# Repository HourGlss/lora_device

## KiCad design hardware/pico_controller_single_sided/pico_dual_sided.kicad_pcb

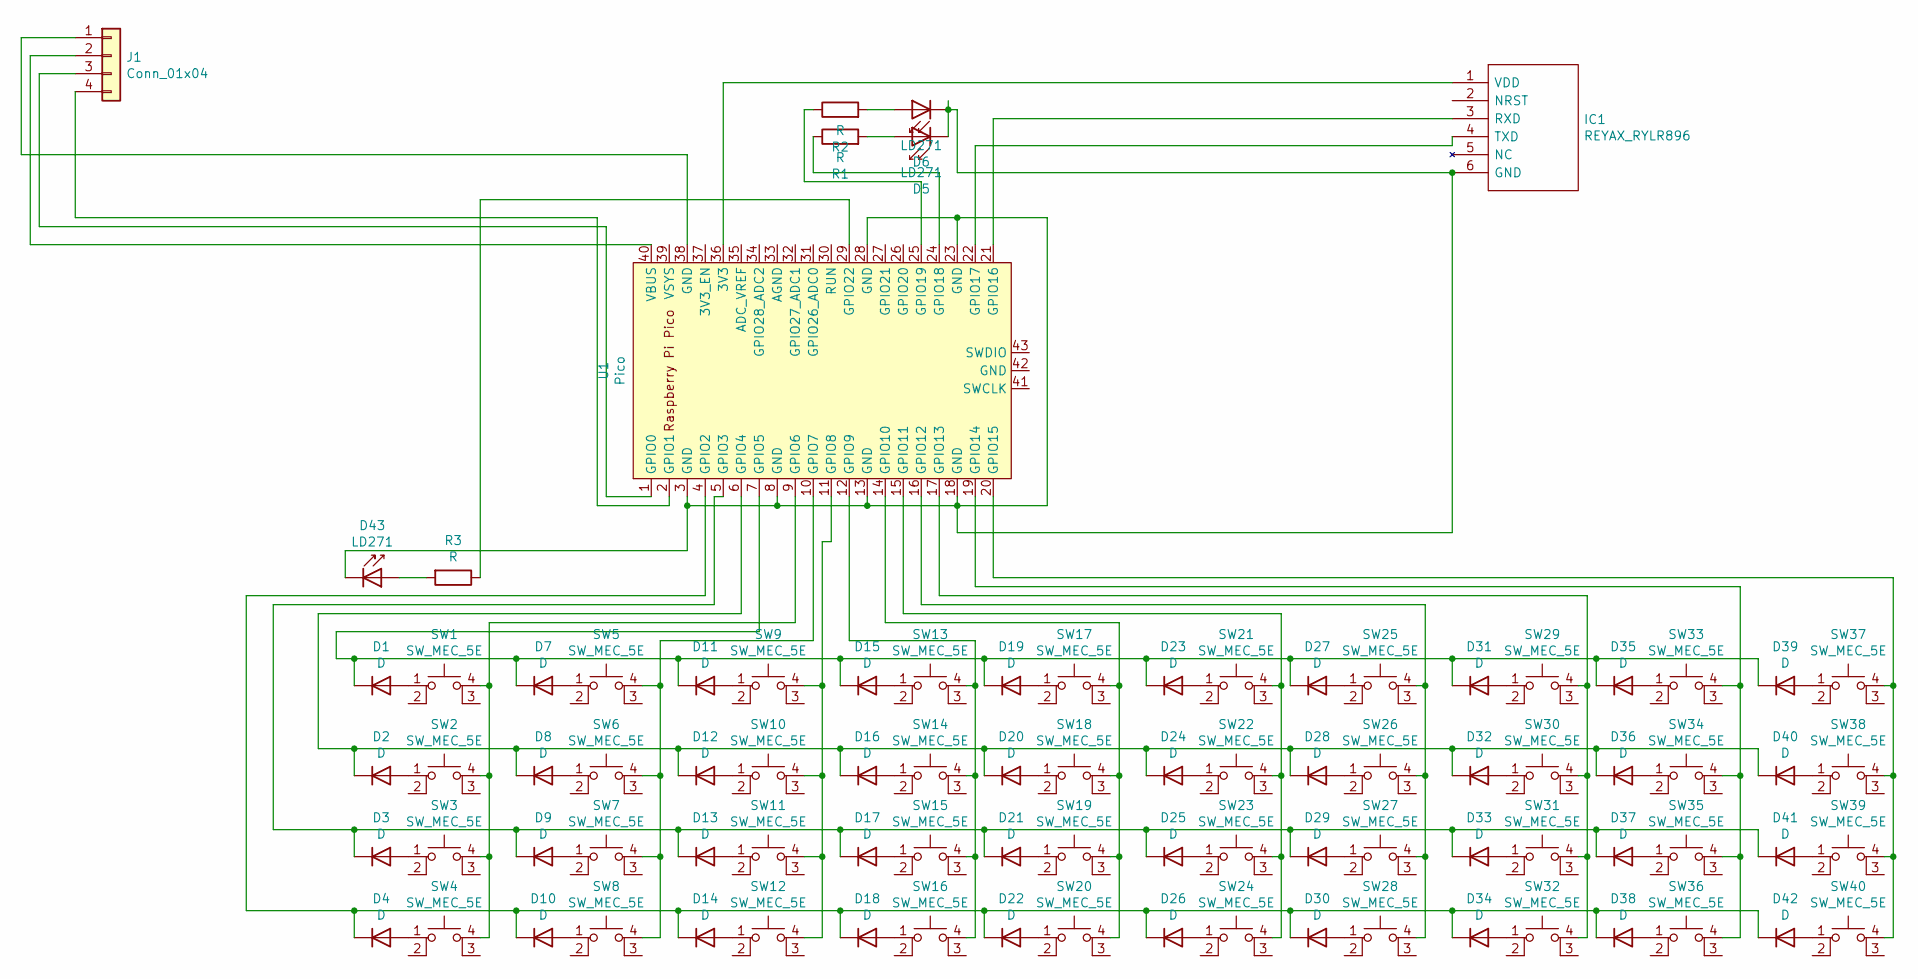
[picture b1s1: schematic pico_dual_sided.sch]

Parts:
D1, D2, D3, D4, D7, D8, D9, D10, D11, D12, D13, D14, D15, D16, D17, D18, D19, D20, D21, D22, D23, D24, D25, D26, D27, D28, D29, D30, D31, D32, D33, D34, D35, D36, D37, D38, D39, D40, D41, D42: D; D_T-1_P5.08mm_Horizontal
D5, D6, D43: LD271; LED_D5.0mm_IRGrey
IC1: REYAX_RYLR896; PinHeader_1x06_P2.54mm_Horizontal; Manufacturer_Part_Number REYAX RYLR896
J1: Conn_01x04; PinHeader_1x04_P2.54mm_Horizontal
R1, R2, R3: R; R_Axial_DIN0204_L3.6mm_D1.6mm_P5.08mm_Horizontal
SW1, SW2, SW3, SW4, SW5, SW6, SW7, SW8, SW9, SW10, SW11, SW12, SW13, SW14, SW15, SW16, SW17, SW18, SW19, SW20, SW21, SW22, SW23, SW24, SW25, SW26, SW27, SW28, SW29, SW30, SW31, SW32, SW33, SW34, SW35, SW36, SW37, SW38, SW39, SW40: SW_MEC_5E; SW_PUSH_6mm_H5mm
U1: Pico; RPi_Pico_SMD_TH

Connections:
unnamed: D1.1 (K), D7.1 (K), D11.1 (K), D15.1 (K), D19.1 (K), D23.1 (K), D27.1 (K), D31.1 (K), D35.1 (K), D39.1 (K), U1.7 (GPIO5)
unnamed: D1.2 (A), SW1.1
unnamed: D2.2 (A), SW2.1
unnamed: D3.2 (A), SW3.1
unnamed: D4.2 (A), SW4.1
unnamed: D5.2 (A), R1.2
unnamed: D6.2 (A), R2.2
unnamed: D7.2 (A), SW5.1
unnamed: D8.2 (A), SW6.1
unnamed: D9.2 (A), SW7.1
unnamed: D4.1 (K), D10.1 (K), D14.1 (K), D18.1 (K), D22.1 (K), D26.1 (K), D30.1 (K), D34.1 (K), D38.1 (K), D42.1 (K), U1.4 (GPIO2)
unnamed: D10.2 (A), SW8.1
unnamed: D11.2 (A), SW9.1
unnamed: D2.1 (K), D8.1 (K), D12.1 (K), D16.1 (K), D20.1 (K), D24.1 (K), D28.1 (K), D32.1 (K), D36.1 (K), D40.1 (K), U1.6 (GPIO4)
unnamed: D12.2 (A), SW10.1
unnamed: D3.1 (K), D9.1 (K), D13.1 (K), D17.1 (K), D21.1 (K), D25.1 (K), D29.1 (K), D33.1 (K), D37.1 (K), D41.1 (K), U1.5 (GPIO3)
unnamed: D13.2 (A), SW11.1
unnamed: D14.2 (A), SW12.1
unnamed: D15.2 (A), SW13.1
unnamed: D16.2 (A), SW14.1
unnamed: D17.2 (A), SW15.1
unnamed: D18.2 (A), SW16.1
unnamed: D19.2 (A), SW17.1
unnamed: D20.2 (A), SW18.1
unnamed: D21.2 (A), SW19.1
unnamed: D22.2 (A), SW20.1
unnamed: D23.2 (A), SW21.1
unnamed: D24.2 (A), SW22.1
unnamed: D25.2 (A), SW23.1
unnamed: D26.2 (A), SW24.1
unnamed: D27.2 (A), SW25.1
unnamed: D28.2 (A), SW26.1
unnamed: D29.2 (A), SW27.1
unnamed: D30.2 (A), SW28.1
unnamed: D31.2 (A), SW29.1
unnamed: D32.2 (A), SW30.1
unnamed: D33.2 (A), SW31.1
unnamed: D34.2 (A), SW32.1
unnamed: D35.2 (A), SW33.1
unnamed: D36.2 (A), SW34.1
unnamed: D37.2 (A), SW35.1
unnamed: D38.2 (A), SW36.1
unnamed: D39.2 (A), SW37.1
unnamed: D40.2 (A), SW38.1
unnamed: D41.2 (A), SW39.1
unnamed: D42.2 (A), SW40.1
unnamed: D5.1 (K), D6.1 (K), D43.1 (K), IC1.6 (GND), U1.3 (GND), U1.8 (GND), U1.13 (GND), U1.18 (GND), U1.23 (GND), U1.28 (GND)
unnamed: D43.2 (A), R3.2
unnamed: IC1.1 (VDD), U1.36 (3V3)
unnamed: IC1.3 (RXD), U1.21 (GPIO16)
unnamed: IC1.4 (TXD), U1.22 (GPIO17)
unnamed: J1.1, U1.38 (GND)
unnamed: J1.2, U1.40 (VBUS)
unnamed: J1.3, U1.1 (GPIO0)
unnamed: J1.4, U1.2 (GPIO1)
unnamed: R1.1, U1.24 (GPIO18)
unnamed: R2.1, U1.25 (GPIO19)
unnamed: R3.1, U1.29 (GPIO22)
unnamed: SW1.4 (A), SW2.4 (A), SW3.4 (A), SW4.4 (A), U1.9 (GPIO6)
unnamed: SW5.4 (A), SW6.4 (A), SW7.4 (A), SW8.4 (A), U1.10 (GPIO7)
unnamed: SW9.4 (A), SW10.4 (A), SW11.4 (A), SW12.4 (A), U1.11 (GPIO8)
unnamed: SW13.4 (A), SW14.4 (A), SW15.4 (A), SW16.4 (A), U1.12 (GPIO9)
unnamed: SW17.4 (A), SW18.4 (A), SW19.4 (A), SW20.4 (A), U1.14 (GPIO10)
unnamed: SW21.4 (A), SW22.4 (A), SW23.4 (A), SW24.4 (A), U1.15 (GPIO11)
unnamed: SW25.4 (A), SW26.4 (A), SW27.4 (A), SW28.4 (A), U1.16 (GPIO12)
unnamed: SW29.4 (A), SW30.4 (A), SW31.4 (A), SW32.4 (A), U1.17 (GPIO13)
unnamed: SW33.4 (A), SW34.4 (A), SW35.4 (A), SW36.4 (A), U1.19 (GPIO14)
unnamed: SW37.4 (A), SW38.4 (A), SW39.4 (A), SW40.4 (A), U1.20 (GPIO15)

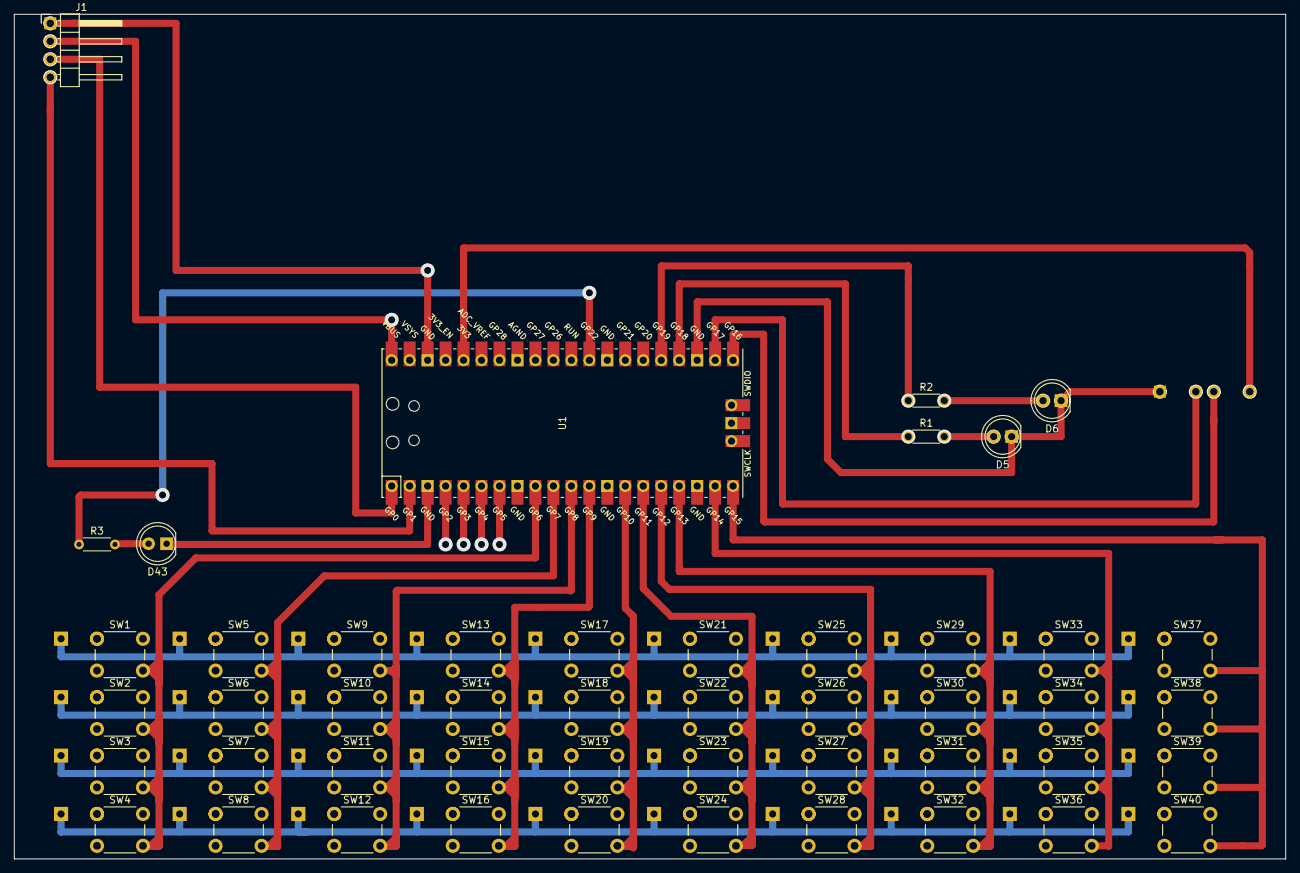
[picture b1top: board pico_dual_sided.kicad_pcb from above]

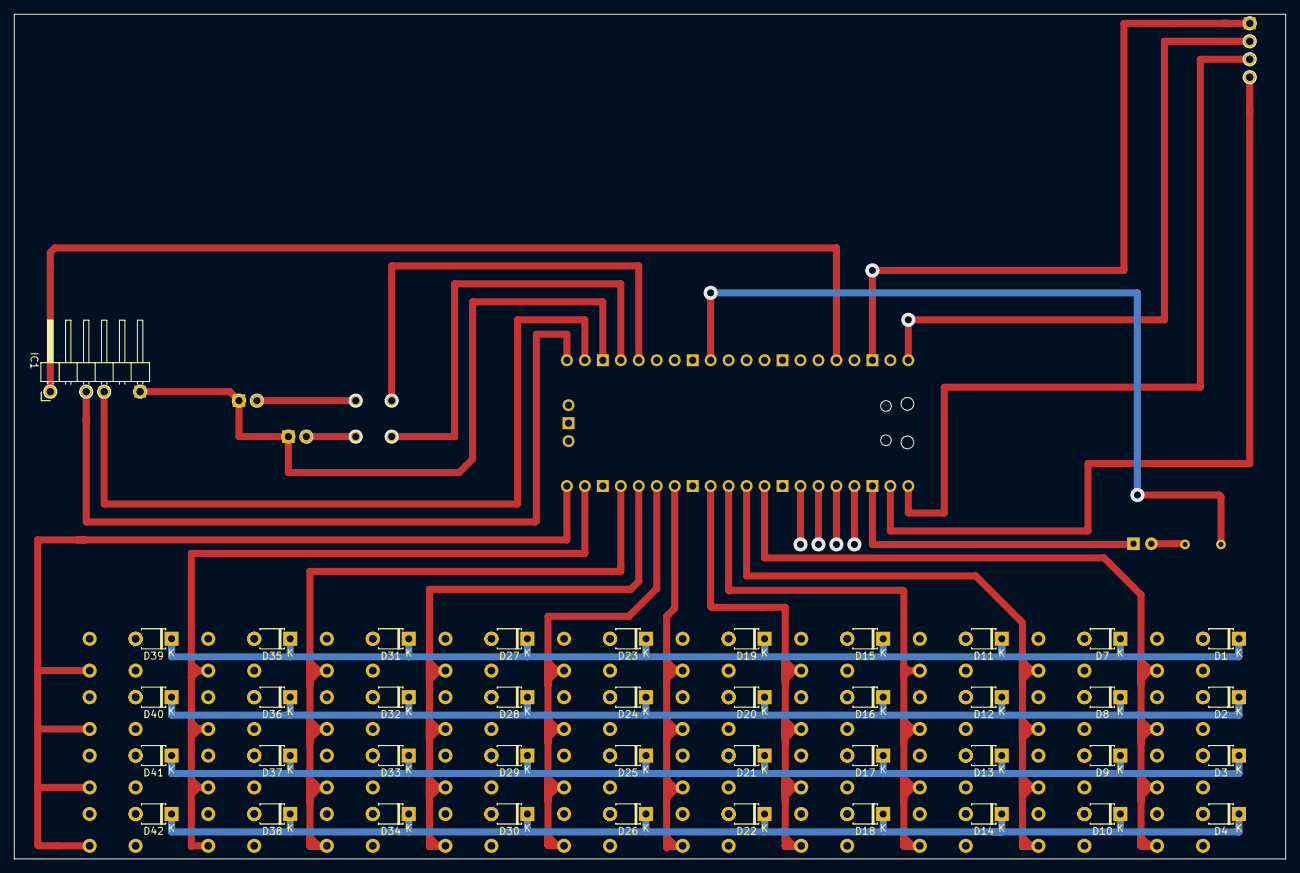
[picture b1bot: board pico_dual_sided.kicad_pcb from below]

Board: 2 copper layers, 179.7 x 119.4 mm, 89 parts (41 on the bottom side), 68 nets.

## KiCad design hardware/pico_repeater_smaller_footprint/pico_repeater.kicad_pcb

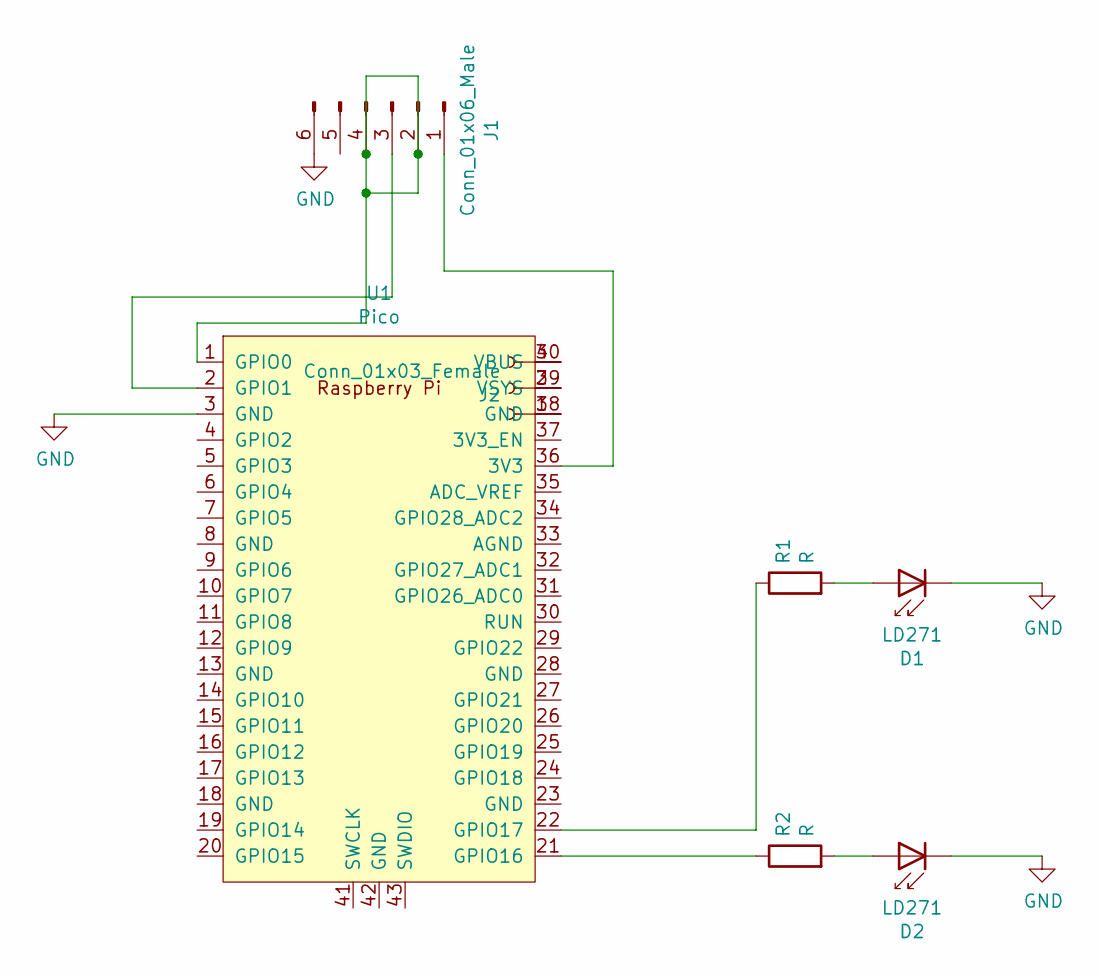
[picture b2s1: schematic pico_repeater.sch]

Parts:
D1, D2: LD271; LED_D5.0mm_IRGrey
J1: Conn_01x06_Male; PinHeader_1x06_P2.54mm_Horizontal
J2: Conn_01x03_Female; PinHeader_1x03_P2.54mm_Horizontal
R1, R2: R; R_Axial_DIN0204_L3.6mm_D1.6mm_P7.62mm_Horizontal
U1: Pico; RPi_Pico_SMD_TH

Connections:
GND: D1.1 (K), D2.1 (K), J1.6, U1.3 (GND)
unnamed: D1.2 (A), R1.2
unnamed: D2.2 (A), R2.2
unnamed: J1.1, U1.36 (3V3)
unnamed: J1.2, J1.4, U1.1 (GPIO0)
unnamed: J1.3, U1.2 (GPIO1)
unnamed: J2.1, U1.38 (GND)
unnamed: J2.2, U1.39 (VSYS)
unnamed: J2.3, U1.40 (VBUS)
unnamed: R1.1, U1.22 (GPIO17)
unnamed: R2.1, U1.21 (GPIO16)

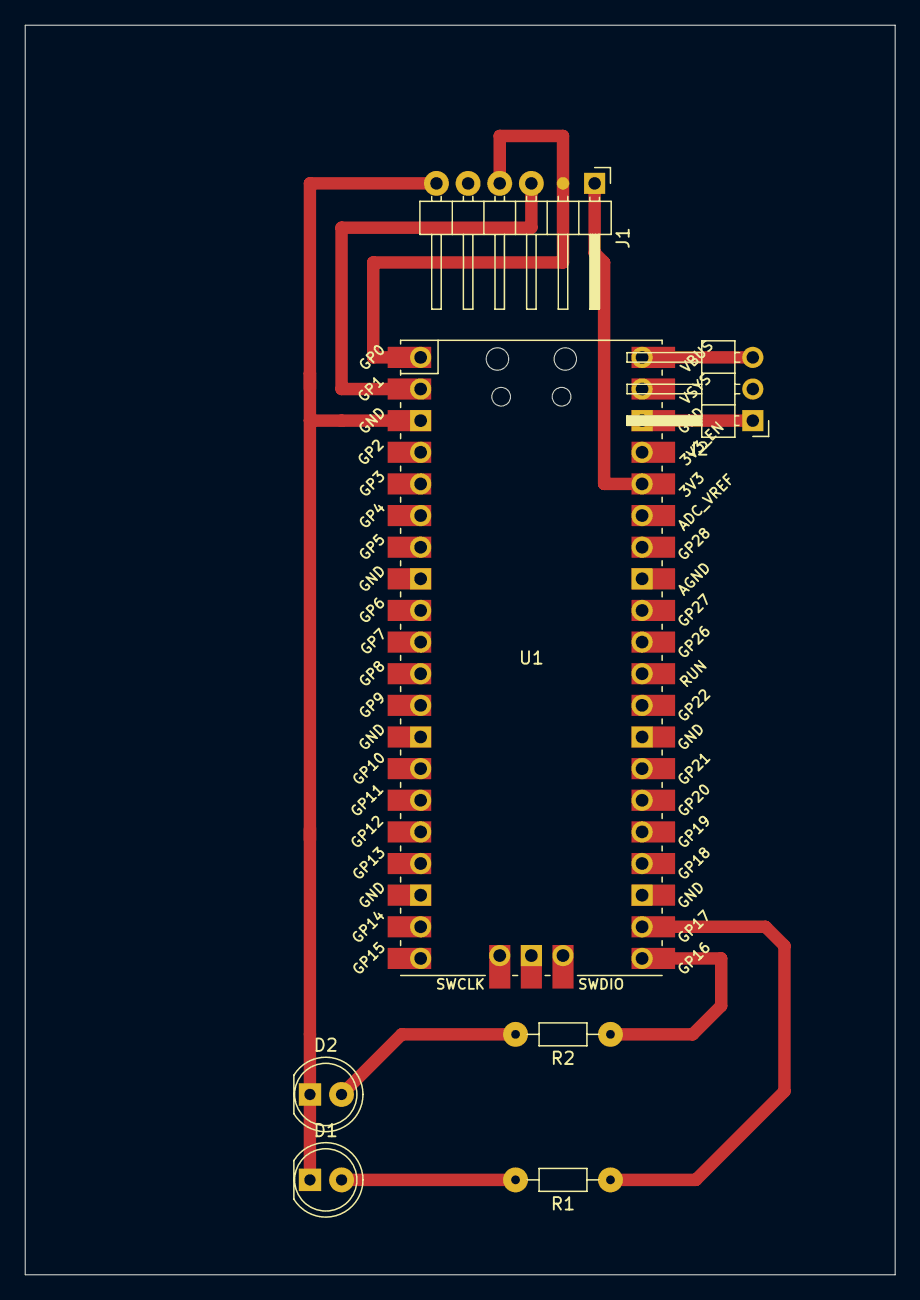
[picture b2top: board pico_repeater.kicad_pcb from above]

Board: 2 copper layers, 69.9 x 100.3 mm, 7 parts (0 on the bottom side), 11 nets.

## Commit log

2021-12-15 changes for fleshman
2021-12-21 updates for msg hash
2021-12-21 broken send before, now it works
2021-12-31 reupdating
2021-12-31 forgot to add state
2022-01-03 Made changes to main_menu added received_menu added settings_menu
2022-01-03 git ignore test
2022-01-03 made a fake keyboard for fleshy
2022-01-03 Making changes to print screen
2022-01-03 While using code with me changes by all users must be checked for commit
2022-01-03 Working on send menu
2022-01-04 attempting to get send_menu working.
2022-01-04 send_menu WORKS.
2022-01-04 changed how the keyboard works with the device.
2022-01-04 Working on ComposeMenu
2022-01-05 removed writechar and delete from ComposeMenu
2022-01-06 changes to structure and addition of hardware items.
2022-01-06 whoops missed these
2022-01-06 added fleshman
2022-01-06 removed logging and inspect from states
2022-01-06 Write character needs work. Also delete does not update properly and the cursor never clears.
2022-01-06 moving stuff around and improving code. implementing the keyboard now.
2022-01-07 ComposeMenu finished
2022-01-07 test
2022-01-07 SendingMenu and SendSuccessful complete
2022-01-07 typing and moving around the states works.
2022-01-08 changes to hardware
2022-01-08 SettingsMenu, SetAddress, and SetNetworkid complete.
2022-01-08 Found a bug in settingsmenu
2022-01-09 ReceivedMenu works. Shows the address of the current message and the message on lines 1 and 2. Currently, message length is limited to 40 characters until I can implement text scrolling.
2022-01-09 whoops. missed this somehow
2022-01-09 whoops. and get item apparently. Its hard to keep track of the code with me commits. Im sorry adam.
2022-01-09 quality of life improvement
2022-01-09 ported States.py to pico code
2022-01-09 Changes by azbai
2022-01-09 changes to support pico usage
2022-01-10 updated flag usage for lcd_event_flag
2022-01-10 adding support for i2c keyboard and fixing bugs
2022-01-10 received menu is broken. also set the default address and network for lora to 5 and 5. also printing the msg when its received for testing
2022-01-15 SendMenu requires on enter after address input, and ComposeMenu bug fixed.
2022-01-15 removed enter from setaddress and setnetworkid
2022-01-15 added SetRFParams with either, less than 3km and more than 3km options
2022-01-16 Sending message would get stuck due to only sending once. Now sends 10 times or goes to SendFailed, whichever comes first.
2022-02-06 Creating a data payload that includes sender and recipient address to be forwarded by the repeater. Still need to deal with duplicate messages in device.py
2022-02-06 Every repeater should nbw fwd a message once. Repeaters echo a received message once and also send the message to the designated recipient stored in the data payload. use .strip("/") to separate send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
2022-02-06 Updated received_menu to accept new data payload
2022-02-07 fixed sending message bug that would get sending message stuck
